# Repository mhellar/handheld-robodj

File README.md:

# Handheld Robo DJ

A pocket robot-voice DJ on an ESP32-S3. **SAM** (the 1982 Software Automatic Mouth speech synth) pre-renders a bank of
words into memory, and a "turntable deck" plays, scratches, stutters and reverses them over a drum machine, with a
16-step sequencer, granular and vocoder voice effects and a sci-fi HUD on a 128x128 OLED. Four buttons, one speaker.

The board is a single-sided PCB designed to be **milled on a desktop CNC** (all copper on the bottom, big pads, no
jumper wires). The modules plug into female headers, so there's no SMD soldering.

## What's in here

| Folder | Contents |
|---|---|
| `firmware/handheld_robodj/` | The Robo DJ sketch (Arduino), SAM's C core bundled alongside |
| `firmware/handheld_bringup/` | Bring-up / test sketch: I2C scan, buttons, joystick, OLED, beep. Flash this first |
| `hardware/kicad/` | KiCad project (schematic, PCB, custom symbols + footprints in `s3_cnc.pretty`) |
| `hardware/cnc/` | Gerbers + Excellon drills, ready-made G-code for a Genmitsu Cubiko (GRBL), the FlatCAM script, a 1:1 print for checking parts fit, and `CNC_CHEATSHEET.txt` |
| `docs/` | Board layout image |

## Parts

| Ref | Part | Notes |
|---|---|---|
| U1 | ESP32-S3 **SuperMini** | 2x 1x9 female headers. One with PSRAM (e.g. 4 MB flash / 2 MB PSRAM) holds the most words |
| U2 | MAX98357A I2S amp breakout | 1x7 female header, VIN on 5 V, plus a small 4-8 ohm speaker |
| U3 | 1.5" 128x128 OLED, **SH1107**, I2C | 1x4 female header (VCC GND SCL SDA), e.g. GME128128-01-IIC |
| U4 | KY-023 joystick module | 1x5 female header. Swap its right-angle pins for straight ones. Not used by Robo DJ, the bring-up sketch tests it |
| SW1-SW4 | 6 mm tact buttons | the diamond: UP / LEFT / RIGHT / DOWN |
| | 100 x 70 mm single-sided copper clad | board is 96 x 66 mm, M3 holes |

## Pinout

| Function | GPIO |
|---|---|
| OLED SDA / SCL | 11 / 12 |
| Amp DIN / BCLK / LRC | 1 / 2 / 3 |
| Buttons UP / RIGHT / LEFT / DOWN | 7 / 6 / 5 / 4 (to GND, internal pull-ups) |
| Joystick X / Y / SW | 10 / 9 / 8 (on 3V3) |

## Build the firmware

1. Arduino IDE (or arduino-cli) with the **ESP32 core 3.x** and the **U8g2** library.
2. Board settings: **ESP32S3 Dev Module**, **USB CDC On Boot: Enabled**, **PSRAM: QSPI PSRAM** (it runs without PSRAM, with fewer words).
   arduino-cli FQBN: `esp32:esp32:esp32s3:CDCOnBoot=cdc,PSRAM=enabled`
3. Open `firmware/handheld_robodj/handheld_robodj.ino` and upload. Flash `handheld_bringup` first if you're bringing up a fresh board.

```
arduino-cli compile --fqbn esp32:esp32:esp32s3:CDCOnBoot=cdc,PSRAM=enabled firmware/handheld_robodj
arduino-cli upload  --fqbn esp32:esp32:esp32s3:CDCOnBoot=cdc,PSRAM=enabled -p COMx firmware/handheld_robodj
```

Tips:
- The OLED uses the `U8G2_SH1107_PIMORONI_128X128` constructor. The generic SH1107 one shifts the picture by 32 px.
- If the SuperMini sits silent after an upload, press its RST button. The auto-reset can leave it in the bootloader.
- Intermittent buttons on a milled board usually turn out to be a solder bridge between neighbouring 2.54 mm pads.
- `handheld_bringup` prints to Serial every 250 ms: run it with a serial monitor open.

## Controls

Diamond: **UP = SHIFT**, **LEFT = VOICE**, **RIGHT = BEAT**, **DOWN = FX**. Live hits play instantly. With REC on they're quantized into the 16 steps.

| Button | tap | double | triple | hold |
|---|---|---|---|---|
| VOICE | say the word | next word | random word | SCRATCH it (tempo-synced) |
| BEAT | kick | snare | clap | hi-hat roll |
| FX | next FX | GROOVE on/off | | STUTTER |
| SHIFT + VOICE | REC on/off | clear voice track | clear all | REVERSE |
| SHIFT + BEAT | next scratch style | tempo | chord progression | TAPE STOP |
| SHIFT + FX | volume | next robot voice (re-renders the words) | | |
| SHIFT alone | MUTATE (new words, same rhythm) | AUTO (random beat + words) | | UNDERWATER |

- **Voice FX:** CLEAN, CRUSH, ECHO, GRAIN (slow cloud of grains at mixed pitches), SWARM (dense detuned robot choir), VOX (16-band vocoder on a chord, words stay clear), CHOIR (pure vocoder).
- **Scratch styles:** BABY, CHIRP, TRANSFORM, TEAR, FLARE.
- **Robot voices:** ROBOT, SAM, ELF, E.T., STUFFY, OLD LADY.
- **Words:** HELLO, ROBOT, YEAH, ERROR, DANCE, BEEP, BOOP, SYSTEM, ONLINE, WOW, FRESH, SCRATCH, ONE-FOUR, OH NO, COMPUTER, PARTY, FUNKY, AWESOME, DOES NOT COMPUTE. Edit `bank[]` in the sketch to make it say anything.

## Make the board

The PCB is single-sided with all copper on **B.Cu**, made for isolation milling. The Gerbers in `hardware/cnc/` also work at
a board house as a 1-layer board.

Milling order (details in `hardware/cnc/CNC_CHEATSHEET.txt`): 0.1 mm 20° V-bit isolation, 1.0 mm drill, 2.0 mm drill,
then V-bit outline score. The `.nc` files are ready to run on a GRBL machine. The drill files are already patched by
`fix_drill_spinup.py`, which fixes the spindle start for GRBL laser mode. To regenerate with FlatCAM, set the
path at the top of `load_and_mirror.tcl` and run it (File > Scripting > Run Script). It mirrors the board, because the
copper is on the bottom.

Before milling, print `PRINT_1to1_fit_test.pdf` at 100% and check your modules against it. The OLED and joystick
outlines were measured from photos.

## Credits and license

- **SAM** (Software Automatic Mouth) by Mark Barton / Don't Ask Software (1982). C port by Sebastian Macke,
  ESP8266SAM by Earle F. Philhower III. The C core is bundled in `firmware/handheld_robodj/`.
- **U8g2** by olikraus; **esp-dsp** and the ESP32 Arduino core by Espressif.
- Co-created by **Mark Hellar** and **Claude** (Anthropic). PCB milled and soldered by Mark Hellar.

Licensed under the **GNU GPL v3** (see `LICENSE`), the same as the bundled SAM core.

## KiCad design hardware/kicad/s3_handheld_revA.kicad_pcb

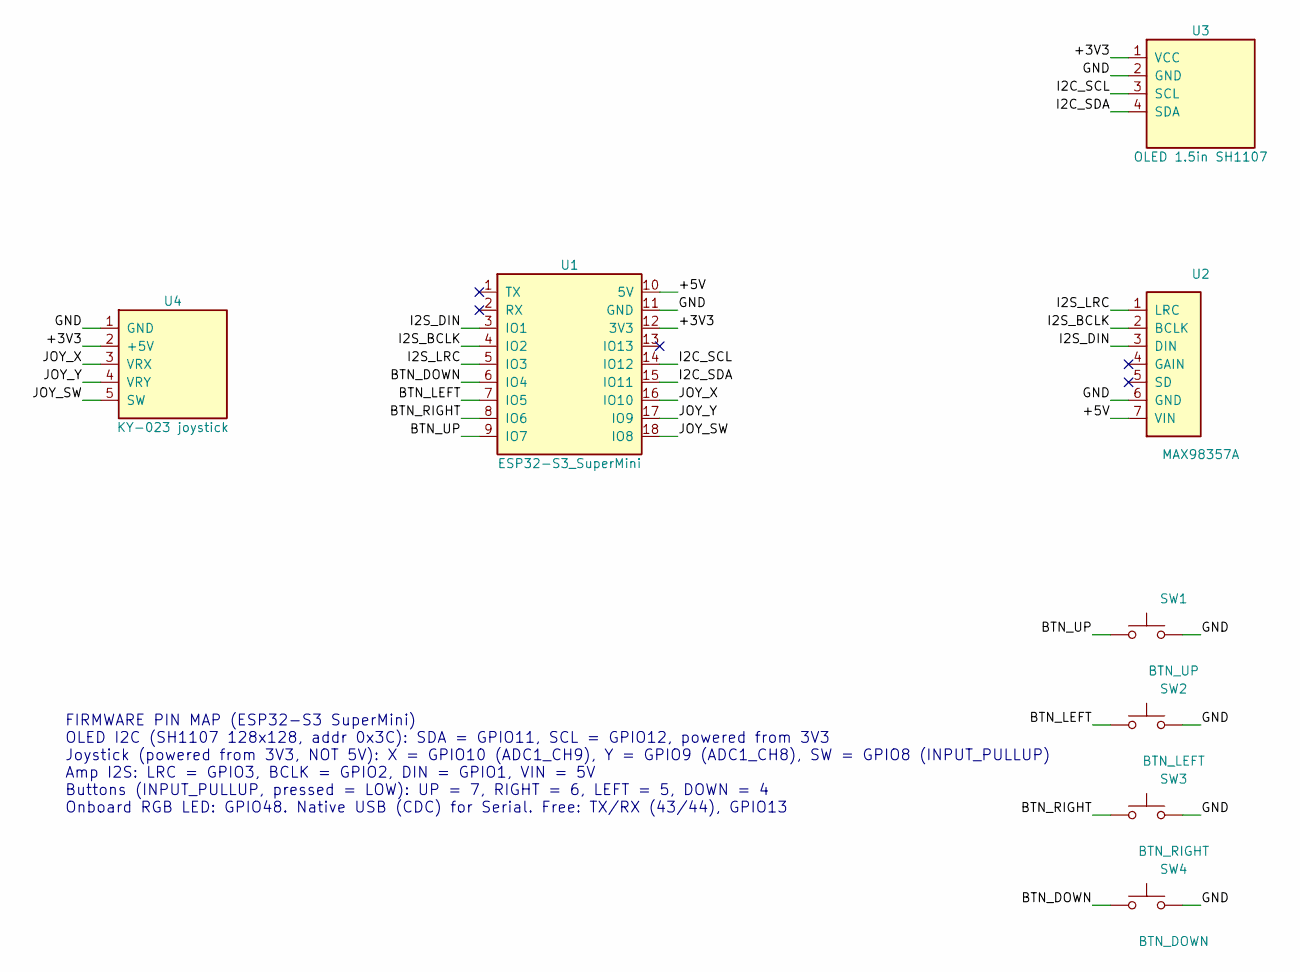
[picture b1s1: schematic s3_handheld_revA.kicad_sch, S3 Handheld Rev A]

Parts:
SW1: BTN_UP; SW_Tact_6mm_CNC
SW2: BTN_LEFT; SW_Tact_6mm_CNC
SW3: BTN_RIGHT; SW_Tact_6mm_CNC
SW4: BTN_DOWN; SW_Tact_6mm_CNC
U1: ESP32-S3_SuperMini; ESP32-S3_SuperMini_CNC
U2: MAX98357A; MAX98357A_Module_CNC
U3: OLED 1.5in SH1107; OLED_1.5in_128x128_I2C_CNC
U4: KY-023 joystick; Joystick_KY023_CNC

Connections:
/+3V3: U1.12 (3V3), U3.1 (VCC), U4.2 (+5V)
/+5V: U1.10 (5V), U2.7 (VIN)
/BTN_DOWN: SW4.1, U1.6 (IO4)
/BTN_LEFT: SW2.1, U1.7 (IO5)
/BTN_RIGHT: SW3.1, U1.8 (IO6)
/BTN_UP: SW1.1, U1.9 (IO7)
/GND: SW1.2, SW2.2, SW3.2, SW4.2, U1.11 (GND), U2.6 (GND), U3.2 (GND), U4.1 (GND)
/I2C_SCL: U1.14 (IO12), U3.3 (SCL)
/I2C_SDA: U1.15 (IO11), U3.4 (SDA)
/I2S_BCLK: U1.4 (IO2), U2.2 (BCLK)
/I2S_DIN: U1.3 (IO1), U2.3 (DIN)
/I2S_LRC: U1.5 (IO3), U2.1 (LRC)
/JOY_SW: U1.18 (IO8), U4.5 (SW)
/JOY_X: U1.16 (IO10), U4.3 (VRX)
/JOY_Y: U1.17 (IO9), U4.4 (VRY)

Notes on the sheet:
FIRMWARE PIN MAP (ESP32-S3 SuperMini) OLED I2C (SH1107 128x128, addr 0x3C): SDA = GPIO11, SCL = GPIO12, powered from 3V3 Joystick (powered from 3V3, NOT 5V): X = GPIO10 (ADC1_CH9), Y = GPIO9 (ADC1_CH8), SW = GPIO8 (INPUT_PULLUP) Amp I2S: LRC = GPIO3, BCLK = GPIO2, DIN = GPIO1, VIN = 5V Buttons (INP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

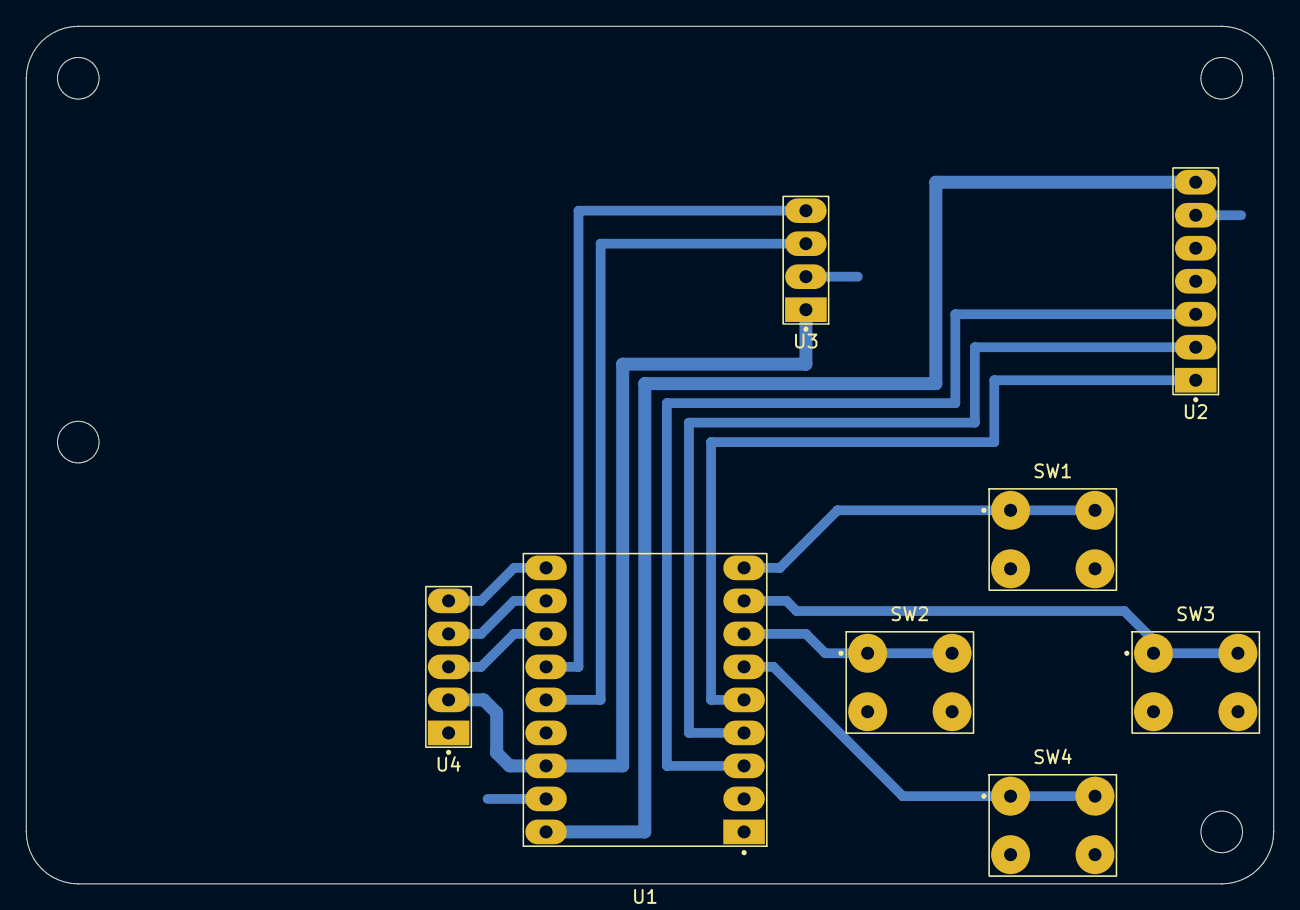
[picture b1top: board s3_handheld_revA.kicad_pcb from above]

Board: 2 copper layers, 96.0 x 66.0 mm, 12 parts (0 on the bottom side), 15 nets.

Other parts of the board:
H1, H2, H3, H4: MountingHole_3.2mm_M3

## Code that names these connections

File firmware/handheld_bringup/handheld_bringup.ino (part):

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
// Pins - straight from the KiCad netlist (s3_handheld_revA)
const int PIN_SDA = 11, PIN_SCL = 12;
const int PIN_JOY_X = 10, PIN_JOY_Y = 9, PIN_JOY_SW = 8;   // joystick powered from 3V3
const int PIN_AMP_LRC = 3, PIN_AMP_BCLK = 2, PIN_AMP_DIN = 1;
const int PIN_RGB = 48;
const bool JOY_SW_ENABLED = true;   // re-enabled 10-02 after the GPIO8 solder blob was cleaned
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  resetWhy = resetReason();
  Serial.printf("\n=== S3 Handheld Rev A bring-up === last reset: %s\n", resetWhy);
  for (int i = 0; i < 4; i++) pinMode(BTN_PINS[i], INPUT_PULLUP);
  if (JOY_SW_ENABLED) pinMode(PIN_JOY_SW, INPUT_PULLUP);
  analogReadResolution(12);
  analogSetPinAttenuation(PIN_JOY_X, ADC_11db);
  analogSetPinAttenuation(PIN_JOY_Y, ADC_11db);

  i2cScan();
  if (oledOk) {
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  if (combo && !comboPrev && oledOk) { rot = (rot + 1) & 3; applyRotation(); }
  comboPrev = combo;

  bool click = JOY_SW_ENABLED && !digitalRead(PIN_JOY_SW);
  int jx = analogRead(PIN_JOY_X), jy = analogRead(PIN_JOY_Y);
  joyFreq = 110.0f * powf(2.0f, jx / 4095.0f * 4.0f);  // 4 octaves, 110..1760 Hz

  static uint32_t lastLed = 0;
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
